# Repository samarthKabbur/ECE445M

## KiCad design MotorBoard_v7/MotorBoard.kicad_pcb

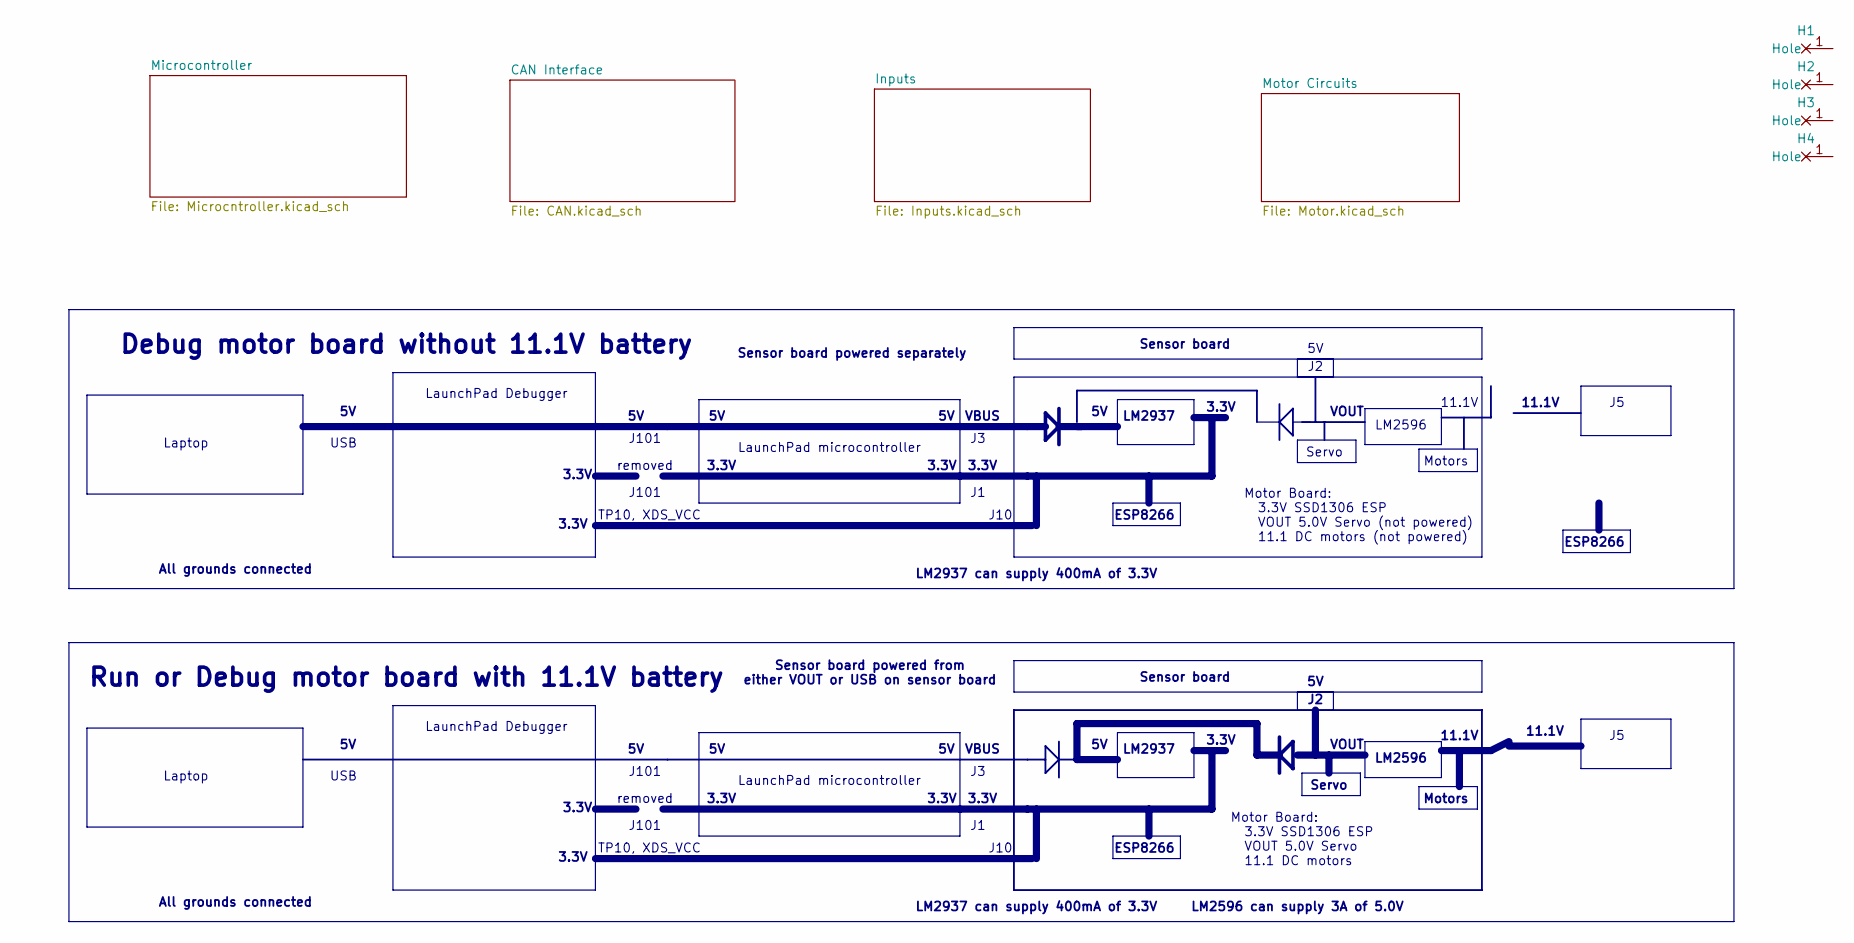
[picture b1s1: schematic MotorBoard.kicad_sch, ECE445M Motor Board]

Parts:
H1, H2, H3, H4: MountingHole_4_40

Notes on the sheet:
3.3V
LM2937 can supply 400mA of 3.3V
Motors
LaunchPad Debugger
USB
Laptop
VOUT
Debug motor board without 11.1V battery
Sensor board
Motor Board: 3.3V SSD1306 ESP VOUT 5.0V Servo 11.1 DC motors
Servo
LM2596 can supply 3A of 5.0V
VBUS
All grounds connected
J10
LM2937
LaunchPad microcontroller
removed
11.1V
Sensor board powered separately
LM2596
TP10, XDS_VCC
Run or Debug motor board with 11.1V battery
J101
Sensor board powered from either VOUT or USB on sensor board
Motor Board: 3.3V SSD1306 ESP VOUT 5.0V Servo (not powered) 11.1 DC motors (not powered)
ESP8266

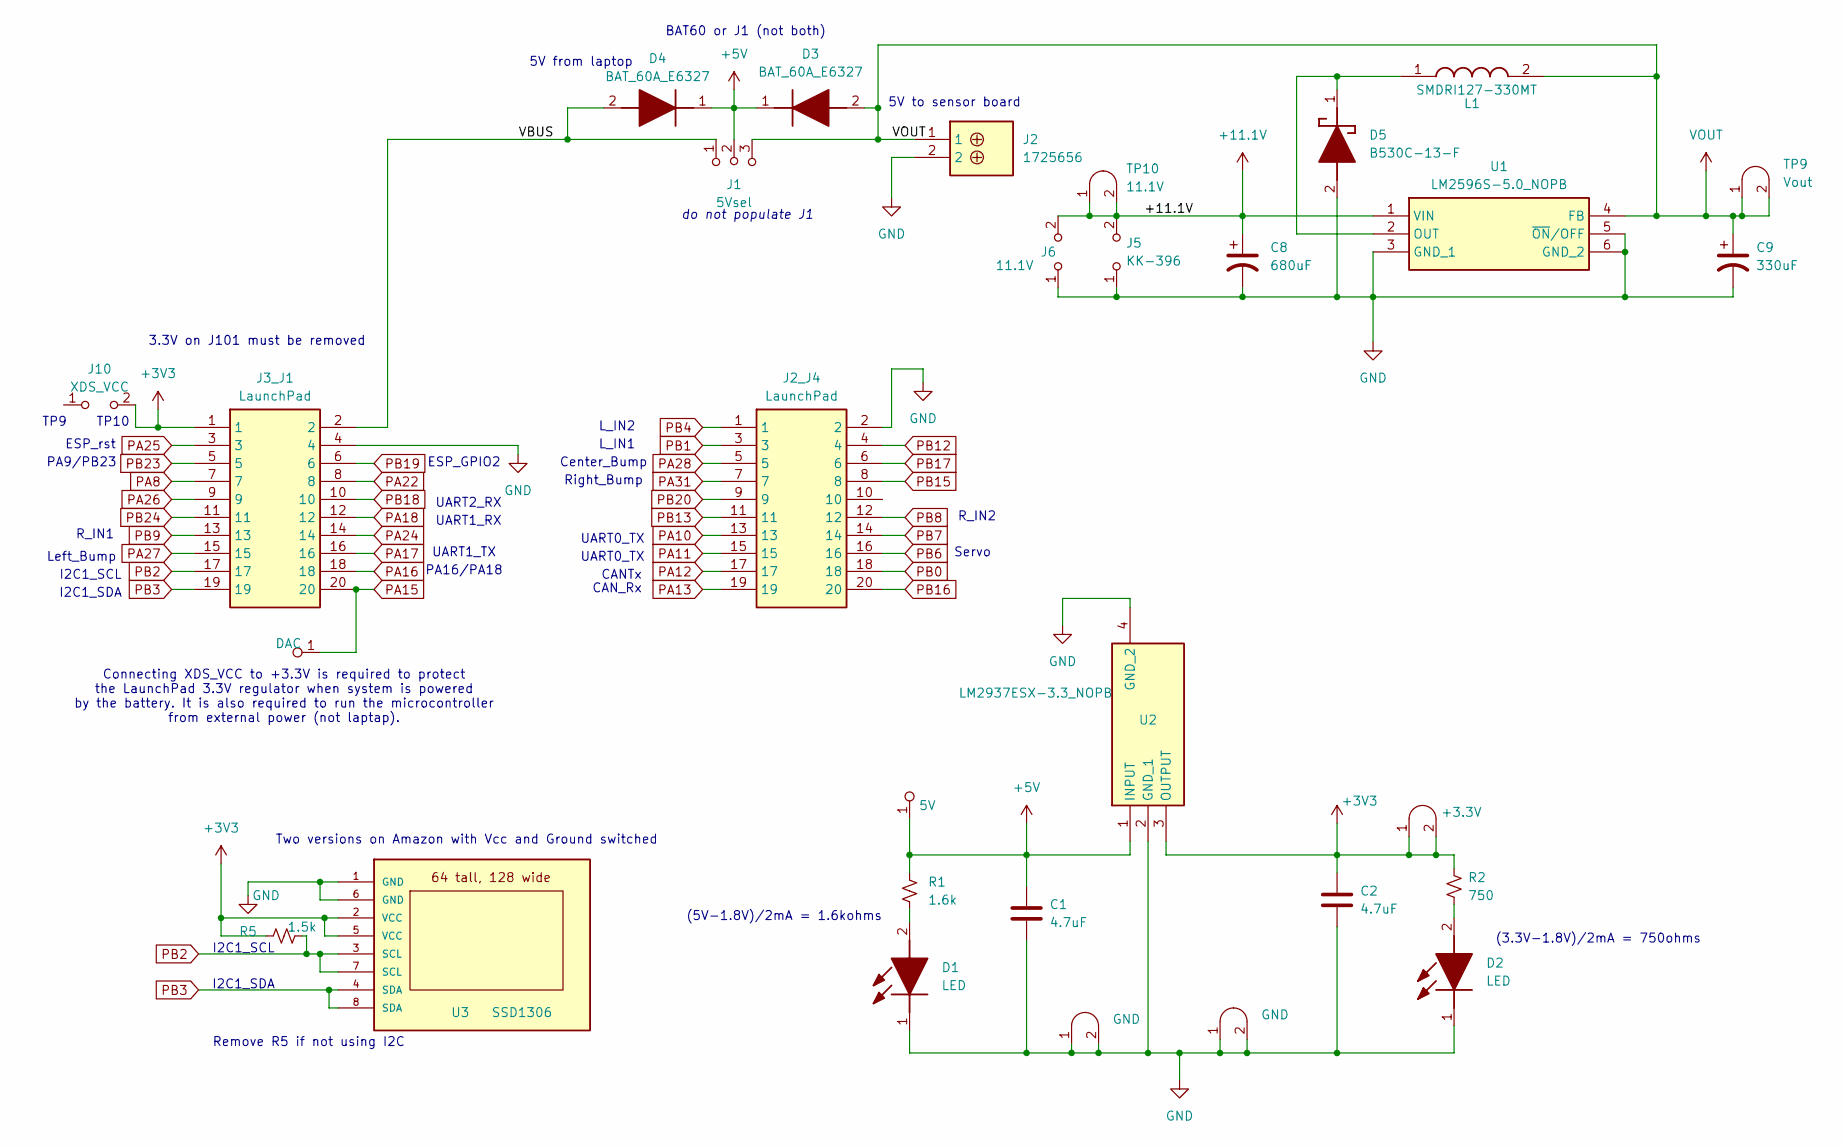
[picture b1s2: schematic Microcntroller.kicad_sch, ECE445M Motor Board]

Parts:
C1, C2: 4.7uF; C_0805_2012Metric; LCSC C5186689
C8: 680uF; CP_Elec_10x10.5; LCSC C2980172
C9: 330uF; CP_Elec_10x10.5; LCSC C5155335
D1, D2: LED; APT1608CGCK; Mouser Part Number 604-APTD1608LSECKJ3F
D3, D4: BAT_60A_E6327; SOD2513X110N; Mouser Part Number 726-BAT60AE6327
D5: B530C-13-F; DO-214AB; Mouser Part Number 621-B530C-13-F
J1: 5Vsel; PinHeader_1x03_P2.54mm_Vertical
J2: 1725656; Mouser Part Number 651-1725656
J2_J4, J3_J1: LaunchPad; Mouser Part Number 855-M20-8761042P
J5: KK-396; Molex_KK-396_A-41792-0002_1x02_P3.96mm_Horizontal
J6: 11.1V; PinHeader_1x02_P2.54mm_Vertical
J10: XDS_VCC; PinHeader_1x02_P2.54mm_Vertical
L1: SMDRI127-330MT; INDPM120120X800N; Mouser Part Number 851-CDRH127LDNP330MC
R1: 1.6k; R_0603_1608Metric; LCSC C340542
R2: 750; R_0603_1608Metric; LCSC C340542
R5: 1.5k; R_0603_1608Metric; LCSC C340542
TP1: DAC; Testpoint_1x1; Digikey 36-5000-ND, 36-5001-ND, 36-5002-ND , 36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
TP2: 5V; Testpoint_1x1; Digikey 36-5000-ND, 36-5001-ND, 36-5002-ND , 36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
TP3: +3.3V; Testpoint_1x02_P2.54mm; Digikey 36-5000-ND, 36-5001-ND, 36-5002-ND , 36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
TP9: Vout; Testpoint_1x02_P2.54mm
TP10: 11.1V; Testpoint_1x02_P2.54mm
TP11, TP16: GND; Testpoint_1x02_P2.54mm
U1: LM2596S-5.0_NOPB; KTT0005B; Mouser Part Number 926-LM2596S-5.0/NOPB
U2: LM2937ESX-3.3_NOPB; SOT230P700X180-4N; Mouser Part Number 926-LM2937IMP3.3NOPB
U3: SSD1306

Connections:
+3V3: C2.1, J3_J1.1, J10.2 (B), R2.1, R5.1, TP3.1 (A), TP3.2 (B), U2.3 (OUTPUT), U3.2 (VCC), U3.5 (VCC); also elsewhere on the board
+5V: C1.1, D3.1 (K), D4.1 (K), J1.2 (B), R1.1, TP2.1 (A), U2.1 (INPUT); also elsewhere on the board
+11.1V: C8.1, J5.2 (B), J6.2 (B), TP10.1 (A), TP10.2 (B), U1.1 (VIN); also elsewhere on the board
/Microcontroller/VBUS: D4.2 (A), J1.1 (A), J3_J1.2
GND: C1.2, C2.2, C8.2, C9.2, D1.1 (K), D2.1 (K), D5.2 (A), J2.2, J2_J4.2, J3_J1.4, J5.1 (A), J6.1 (A), TP11.1 (A), TP11.2 (B), TP16.1 (A), TP16.2 (B), U1.3 (GND_1), U1.5 (~ON/OFF), U1.6 (GND_2), U2.2 (GND_1), U2.4 (GND_2), U3.1 (GND), U3.6 (GND); also elsewhere on the board
unnamed: D1.2 (A), R1.2
unnamed: D2.2 (A), R2.2
unnamed: D5.1 (K), L1.1, U1.2 (OUT)
PA8: J3_J1.7
PA10: J2_J4.13
PA11: J2_J4.15
PA12: J2_J4.17; also elsewhere on the board
PA13: J2_J4.19; also elsewhere on the board
PA15: J3_J1.20, TP1.1 (A)
PA16: J3_J1.18
PA17: J3_J1.16; also elsewhere on the board
PA18: J3_J1.12; also elsewhere on the board
PA22: J3_J1.8
PA24: J3_J1.14
PA25: J3_J1.3; also elsewhere on the board
PA26: J3_J1.9
PA27: J3_J1.15; also elsewhere on the board
PA28: J2_J4.5; also elsewhere on the board
PA31: J2_J4.7; also elsewhere on the board
PB0: J2_J4.18
PB1: J2_J4.3; also elsewhere on the board
PB2: J3_J1.17, R5.2, U3.3 (SCL), U3.7 (SCL)
PB3: J3_J1.19, U3.4 (SDA), U3.8 (SDA)
PB4: J2_J4.1; also elsewhere on the board
PB6: J2_J4.16; also elsewhere on the board
PB7: J2_J4.14
PB8: J2_J4.12; also elsewhere on the board
PB9: J3_J1.13; also elsewhere on the board
PB12: J2_J4.4
PB13: J2_J4.11
PB15: J2_J4.8
PB16: J2_J4.20
PB17: J2_J4.6
PB18: J3_J1.10
PB19: J3_J1.6; also elsewhere on the board
PB20: J2_J4.9
PB23: J3_J1.5
PB24: J3_J1.11
VOUT: C9.1, D3.2 (A), J1.3 (C), J2.1, L1.2, TP9.1 (A), TP9.2 (B), U1.4 (FB); also elsewhere on the board

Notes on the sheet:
TP10
UART0_TX
UART1_RX
(5V-1.8V)/2mA = 1.6kohms
(3.3V-1.8V)/2mA = 750ohms
Left_Bump
5V from laptop
ESP_GPIO2
UART2_RX
CANTx
UART1_TX
Right_Bump
3.3V on J101 must be removed
L_IN1
Servo
Center_Bump
I2C1_SDA
PA16/PA18
BAT60 or J1 (not both)
Remove R5 if not using I2C
TP9
do not populate J1
R_IN2
PA9/PB23
I2C1_SCL
5V to sensor board
R_IN1
CAN_Rx
ESP_rst
Two versions on Amazon with Vcc and Ground switched
Connecting XDS_VCC to +3.3V is required to protect the LaunchPad 3.3V regulator when system is powered by the battery. It is also required to run the microcontroller from external power (not laptap).
L_IN2

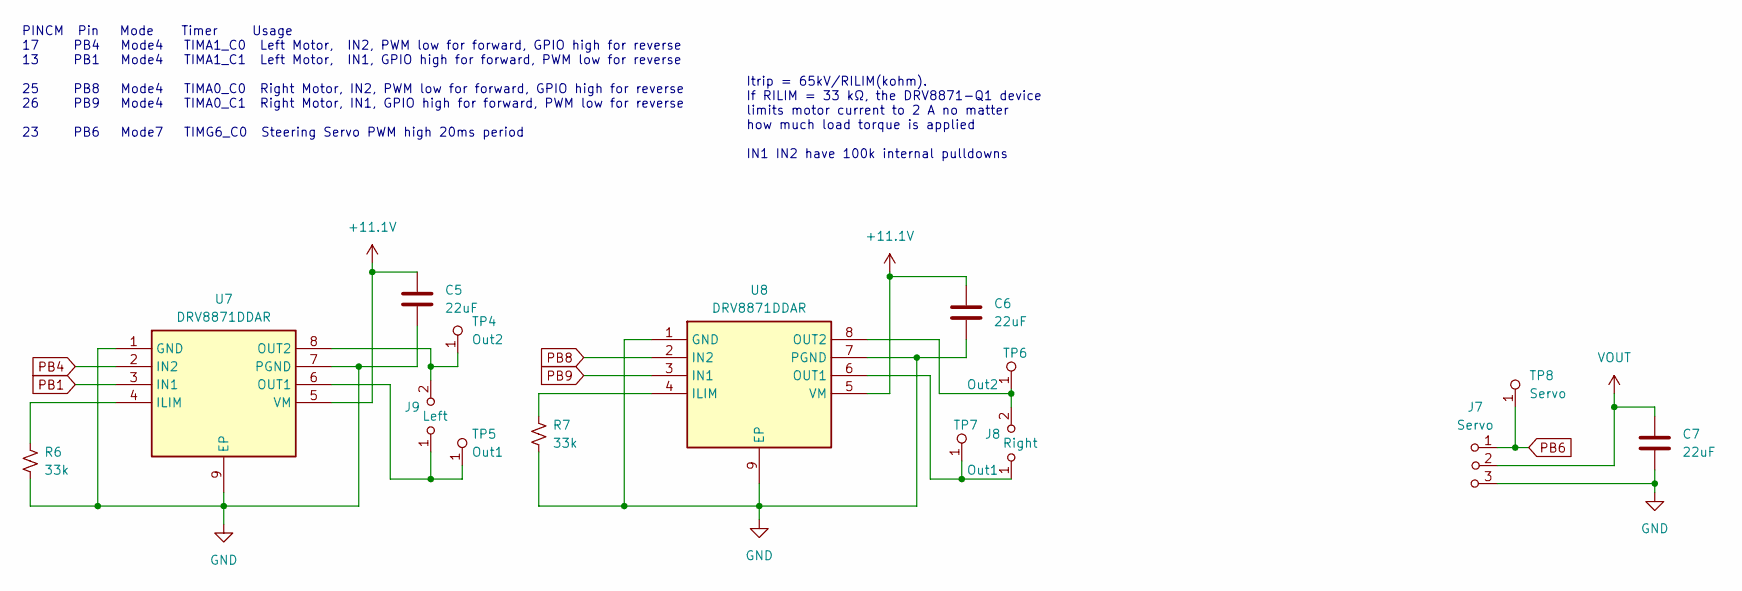
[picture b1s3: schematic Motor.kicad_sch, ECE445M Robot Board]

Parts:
C5, C6, C7: 22uF; C_0805_2012Metric; LCSC C5186689
J7: Servo; PinHeader_1x03_P2.54mm_Vertical
J8: Right; Molex_KK-396_5273-02A_1x02_P3.96mm_Vertical
J9: Left; Molex_KK-396_5273-02A_1x02_P3.96mm_Vertical
R6, R7: 33k; R_0603_1608Metric; LCSC C340542
TP4, TP6: Out2; Testpoint_1x1; Digikey 36-5000-ND, 36-5001-ND, 36-5002-ND , 36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
TP5, TP7: Out1; Testpoint_1x1; Digikey 36-5000-ND, 36-5001-ND, 36-5002-ND , 36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
TP8: Servo; Testpoint_1x1; Digikey 36-5000-ND, 36-5001-ND, 36-5002-ND , 36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
U7, U8: DRV8871DDAR; SOIC127P600X170-9N; Mouser Part Number 595-DRV8871DDAR

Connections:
+11.1V: C5.1, C6.1, U7.5 (VM), U8.5 (VM); also elsewhere on the board
GND: C5.2, C6.2, C7.2, J7.3 (C), R6.2, R7.2, U7.1 (GND), U7.7 (PGND), U7.9 (EP), U8.1 (GND), U8.7 (PGND), U8.9 (EP); also elsewhere on the board
unnamed: J8.1 (A), TP7.1 (A), U8.6 (OUT1)
unnamed: J8.2 (B), TP6.1 (A), U8.8 (OUT2)
unnamed: J9.1 (A), TP5.1 (A), U7.6 (OUT1)
unnamed: J9.2 (B), TP4.1 (A), U7.8 (OUT2)
unnamed: R6.1, U7.4 (ILIM)
unnamed: R7.1, U8.4 (ILIM)
PB1: U7.3 (IN1); also elsewhere on the board
PB4: U7.2 (IN2); also elsewhere on the board
PB6: J7.1 (A), TP8.1 (A); also elsewhere on the board
PB8: U8.2 (IN2); also elsewhere on the board
PB9: U8.3 (IN1); also elsewhere on the board
VOUT: C7.1, J7.2 (B); also elsewhere on the board

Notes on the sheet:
PINCM Pin Mode Timer Usage 17 PB4 Mode4 TIMA1_C0 Left Motor, IN2, PWM low for forward, GPIO high for reverse 13 PB1 Mode4 TIMA1_C1 Left Motor, IN1, GPIO high for forward, PWM low for reverse 25 PB8 Mode4 TIMA0_C0 Right Motor, IN2, PWM low for forward, GPIO high for reverse 26 PB9 Mode4 TIMA0_C1 Rig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
Itrip = 65kV/RILIM(kohm). If RILIM = 33 kΩ, the DRV8871-Q1 device limits motor current to 2 A no matter how much load torque is applied IN1 IN2 have 100k internal pulldowns

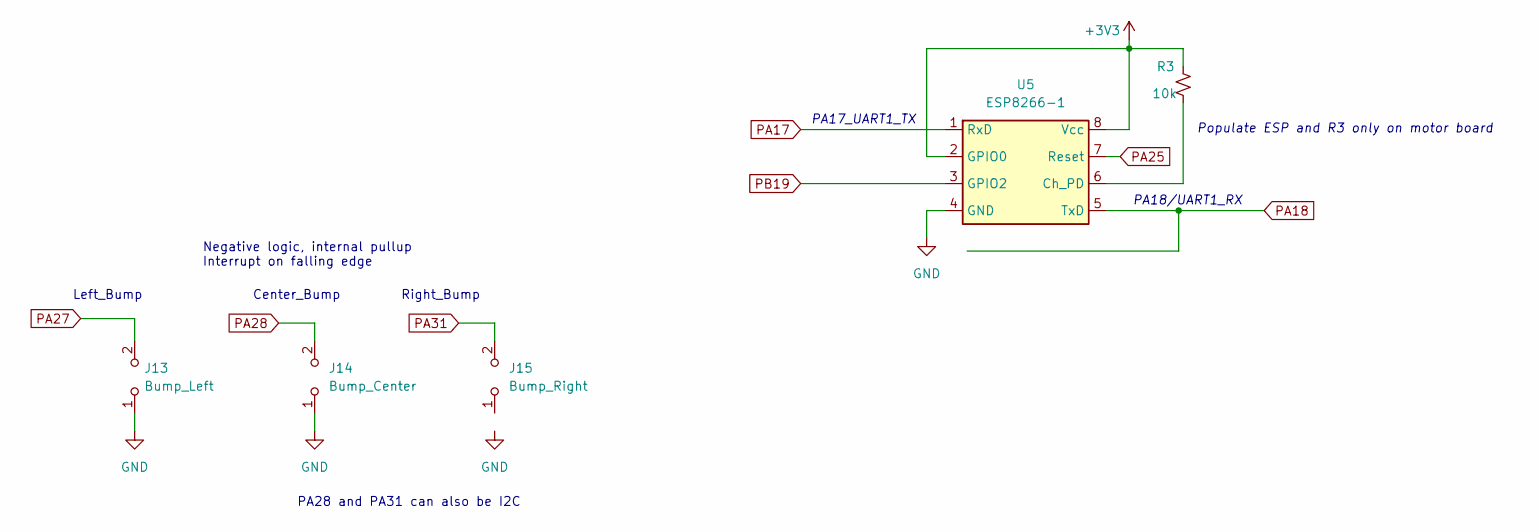
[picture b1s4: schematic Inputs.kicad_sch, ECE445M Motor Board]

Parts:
J13: Bump_Left; PinHeader_1x02_P2.54mm_Vertical
J14: Bump_Center; PinHeader_1x02_P2.54mm_Vertical
J15: Bump_Right; PinHeader_1x02_P2.54mm_Vertical
R3: 10k; R_0603_1608Metric
U5: ESP8266-1; PinHeader_2x04_P2.54mm_Vertical

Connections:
+3V3: R3.1, U5.2 (GPIO0), U5.8 (Vcc); also elsewhere on the board
GND: J13.1 (A), J14.1 (A), U5.4 (GND); also elsewhere on the board
unnamed: R3.2, U5.6 (Ch_PD)
PA17: U5.1 (RxD); also elsewhere on the board
PA18: U5.5 (TxD); also elsewhere on the board
PA25: U5.7 (Reset); also elsewhere on the board
PA27: J13.2 (B); also elsewhere on the board
PA28: J14.2 (B); also elsewhere on the board
PA31: J15.2 (B); also elsewhere on the board
PB19: U5.3 (GPIO2); also elsewhere on the board

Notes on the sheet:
Center_Bump
Populate ESP and R3 only on motor board
PA17_UART1_TX
PA18/UART1_RX
PA28 and PA31 can also be I2C
Negative logic, internal pullup Interrupt on falling edge
Left_Bump
Right_Bump

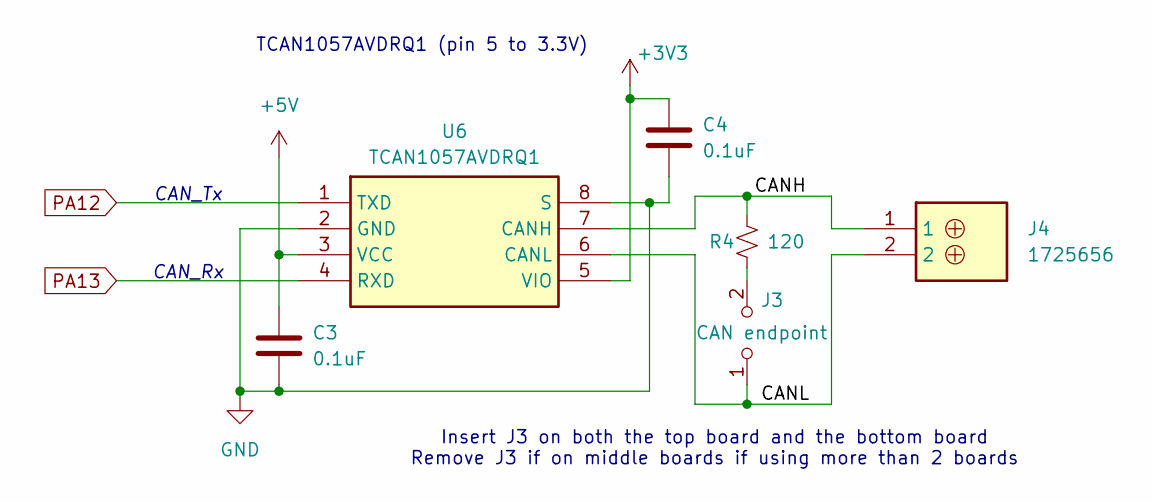
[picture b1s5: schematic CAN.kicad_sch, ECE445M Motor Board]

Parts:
C3, C4: 0.1uF; C_0603_1608Metric; LCSC C5186689
J3: CAN endpoint; PinHeader_1x02_P2.54mm_Vertical
J4: 1725656; Mouser Part Number 651-1725656
R4: 120; R_0603_1608Metric; LCSC C340542
U6: TCAN1057AVDRQ1; SOIC127P600X175-8N; Mouser Part Number 595-TCAN1057AVDRQ1

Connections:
+3V3: C4.1, U6.5 (VIO); also elsewhere on the board
+5V: C3.1, U6.3 (VCC); also elsewhere on the board
/CAN Interface/CANH: J4.1, R4.1, U6.7 (CANH)
/CAN Interface/CANL: J3.1 (A), J4.2, U6.6 (CANL)
GND: C3.2, C4.2, U6.2 (GND), U6.8 (S); also elsewhere on the board
unnamed: J3.2 (B), R4.2
PA12: U6.1 (TXD); also elsewhere on the board
PA13: U6.4 (RXD); also elsewhere on the board

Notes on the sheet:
Insert J3 on both the top board and the bottom board Remove J3 if on middle boards if using more than 2 boards
CAN_Tx
TCAN1057AVDRQ1 (pin 5 to 3.3V)
CAN_Rx

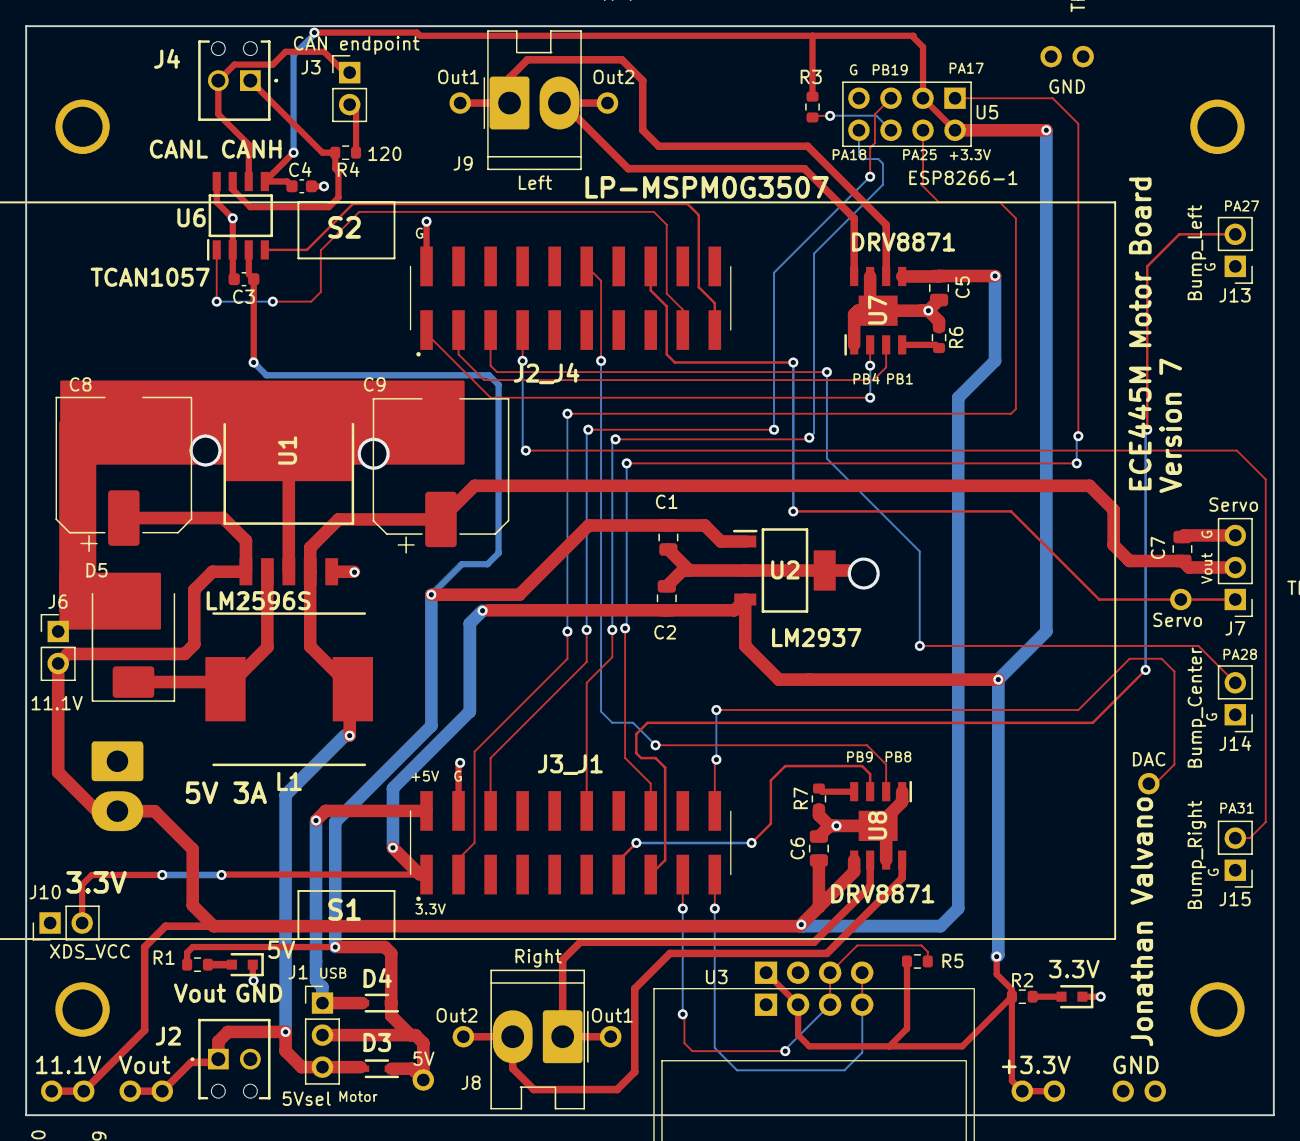
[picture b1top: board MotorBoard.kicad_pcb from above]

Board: 2 copper layers, 98.9 x 86.4 mm, 60 parts (1 on the bottom side), 36 nets.

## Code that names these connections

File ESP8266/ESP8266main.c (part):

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 |                        4   5 |
 \------------------------------/ 
 Connects MSPM0 
    UART1 on (PA17/PA18) or UART2 on (PB17/PB18)
    Reset on PA25
    Ok to not access PB19 because of the internal pullup in ESP8266
 ESP8266    MSPM0     Motor board version 7
  1 URxD    PA17      UART1 out of MSPM0, into ESP8266 115200 baud
  2 GPIO0             +3.3V for normal operation (ground to flash)
  3 GPIO2   PB19      GPIO, high/float on startup, has internal pullup, can be used for I/O
  4 GND     Gnd       GND (70mA)
  5 UTxD    PA18      UART out of ESP8266, UART1 into MSPM0 115200 baud
  6 Ch_PD             chip select, 10k resistor to 3.3V
  7 Reset   PA25      MSPM0 GPIO output, can issue output low to cause hardware reset
  8 Vcc               regulated 3.3V supply with at least 70mA

 ESP8266    MSPM0     Motor board version 7.1
  1 URxD    PB17      UART2 out of MSPM0, into ESP8266 115200 baud
  2 GPIO0             +3.3V for normal operation (ground to flash)
  3 GPIO2   PB19      GPIO, high/float on startup, has internal pullup, can be used for I/O
  4 GND     Gnd       GND (70mA)
  5 UTxD    PB18      UART out of ESP8266, UART2 into MSPM0 115200 baud
  6 Ch_PD             chip select, 10k resistor to 3.3V
  7 Reset   PA25      MSPM0 GPIO output, can issue output low to cause hardware reset
  8 Vcc               regulated 3.3V supply with at least 70mA
 */
 /* Derived from i2c_controller_rw_multibyte_fifo_poll_LP_MSPM0G3507_nortos_ticlang
  VCC to +3.3V
  I2C SCL: PB2 is the SSD1306 SCL, with 1.5k pullup to 3.3V
  I2C SDA: PB3 is the SSD1306 SDA
  GND to GND
*/

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
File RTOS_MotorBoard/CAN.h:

// CAN.h
// Runs on MSPM0G3507
// Use FDCAN0 to communicate on CAN bus PA12 and PA13
// 

// Jonathan Valvano
// December 11, 2025
// derived from can_to_uart_bridge_LP_MSPM0G3507_nortos_ticlang
/* 
 Copyright 2025 by Jonathan W. Valvano, valvano@mail.utexas.edu
    You may use, edit, run or distribute this file
    as long as the above copyright notice remains
 THIS SOFTWARE IS PROVIDED "AS IS".  NO WARRANTIES, WHETHER EXPRESS, IMPLIED
 OR STATUTORY, INCLUDING, BUT NOT LIMITED TO, IMPLIED WARRANTIES OF
 MERCHANTABILITY AND FITNESS FOR A PARTICULAR PURPOSE APPLY TO THIS SOFTWARE.
 VALVANO SHALL NOT, IN ANY CIRCUMSTANCES, BE LIABLE FOR SPECIAL, INCIDENTAL,
 OR CONSEQUENTIAL DAMAGES, FOR ANY REASON WHATSOEVER.
 For more information about my classes, my research, and my books, see
 http://users.ece.utexas.edu/~valvano/
 */
// Use TCAN1057AVDRQ1 (not TCAN1057A-Q1, the version with pin 5 nc)
//  Pin1 TXD  ---- CAN_Tx PA12 FD-CAN module 0 transmit
//  Pin2 Vss  ---- ground
//  Pin3 VCC  ---- +5V with 0.1uF cap to ground
//  Pin4 RXD  ---- CAN_Rx PA13 FD-CAN module 0 receive (0 to 3.3V)
//  Pin5 VIO  ---- +3.3V (digital interface supply)
//  Pin6 CANL ---- to other CANL on network 
//  Pin7 CANH ---- to other CANH on network 
//  Pin8 RS   ---- ground, Slope-Control Input (maximum slew rate)
// 120 ohm across CANH, CANL on both ends of network

#ifndef __CAN_H__
#define __CAN_H__
#include "../RTOS_Labs_common/OS.h"
#include <stdint.h>

void CAN_Init(uint32_t priority);

void CAN_EnableInterrupts(uint32_t priority);

/*
// 0 if failure
// 1 if ok
int CAN_Send(uint32_t id, uint32_t dlc, uint8_t *data);

// Returns 1 if receive data is available
//         0 if no receive data ready
int CAN_CheckMail(void);

// if receive data is ready, gets the data and returns true
// if no receive data is ready, returns false
int CAN_GetMailNonBlock(uint32_t *id, uint32_t *dlc, uint8_t *data);

// if receive data is ready, gets the data 
// if no receive data is ready, it waits until it is ready
void CAN_GetMail(uint32_t *id, uint32_t *dlc, uint8_t *data);
*/

/***************Added Functionality**************/
// CAN functions can be called from anywhere
// These function will NOT block and wait

// Gets value from receive FIFO
// Returns 1 if successful
// Returns 0 if failed
uint32_t CAN_Get(uint32_t *data);
uint32_t CAN_Get_ID(uint32_t *data, uint32_t *id);

// Puts a value into the send FIFO
// Returns 1 if successful
// Returns 0 if failed
uint32_t CAN_Put(uint32_t id, uint32_t data);

// Should be power of 2
#define CANFIFORECEIVESIZE 16

/* CAN FIFO */
typedef struct CAN_Fifo {
  uint32_t PutI;
  uint32_t GetI;
  uint32_t data[CANFIFORECEIVESIZE];
} CAN_Fifo_t;

CAN_Fifo_t CAN_SendFifo;
CAN_Fifo_t CAN_ReceiveFifo;

Sema4_t CAN_Available;

#endif //  __CAN_H__

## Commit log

2026-01-29 lab 1 in progress
2026-01-30 removed comments
2026-01-30 finished lab 1
2026-02-02 started lab 2
2026-02-02 round robin thread switch works
2026-02-02 systick simply requests pendsv and utilizes tail chaining
2026-02-02 lab 2 done
2026-02-04 stop tracking unnecessary files
2026-02-04 lab 2.2 pre prep, currently hardfaults
2026-02-07 os_kill currently leads to hardfault
2026-02-08 os kill works
2026-02-08 lab 2-2 pre prep done
2026-02-09 background task scheduler works!
2026-02-09 add s2 task works
2026-02-09 lab2 interpreter.c-not checked
2026-02-09 implemented mailbox init
2026-02-09 implemented mailbox send
2026-02-09 implemented mailbox recv
2026-02-09 implemented fifo init and updated mailbox init
2026-02-09 implemented fifo get
2026-02-09 merged interpreter in
2026-02-09 fifo works
2026-02-09 added semaphores to software fifos
2026-02-09 updated software fifo with semaphores and added mailbox test case
2026-02-09 mail box works
2026-02-09 interpreter works
2026-02-09 testing display
2026-02-09 everything works lab 2 except jitter
2026-02-11 hard faulting
2026-02-11 stack initializes to amount defined in os addthread parameter. prevents hardfault
2026-02-14 implemented add s1 task
2026-02-14 added compile time switch for debugging instruments
2026-02-16 fixed some jitter and just added debugging
2026-02-16 jitter reduces when timg8=500 period
2026-02-16 still debugging jitter
2026-02-21 Implemented priority scheduler and sorted TCB insertion
2026-02-22 testmain3 works
2026-02-22 working on test4 only periodic priority done
2026-02-23 updated wait, signal, kill, scheduler
2026-02-23 test main 5 works
2026-02-23 Update OS.c before merging
2026-02-25 moving back to align with olyvia's branch
2026-02-25 not working testfifo
2026-02-25 Testmain 4, 5, FIFO all work
2026-02-25 testmain7
2026-02-25 interpreter changes for lab 3
2026-03-02 started lab 4
2026-03-03 previous lab 3 final commit and lab 4 interpret stuff
2026-03-04 fat and directory defined
2026-03-04 eFile_Init() written
2026-03-04 started writing format
2026-03-04 Update filesystem and interpreter changes
2026-03-05 updated directory functions
2026-03-07 bitmap and filesystem_t added
2026-03-07 wrote efile_create. replaced directory_t with filesystem_t across the program
2026-03-07 wrote efile_wopen
2026-03-08 read functions
2026-03-08 testmain2 works
2026-03-08 testmain3
2026-03-09 lab4 done but need to fix jitter
2026-03-09 cleared commented sections
2026-03-10 final lab 4
2026-03-13 add deadline
2026-03-13 wrote heap definition as static array
2026-03-20 wrote heap init
2026-03-20 untested malloc
2026-03-20 working on malloc merge
2026-03-21 wrote malloc
2026-03-21 updated malloc
2026-03-21 updates to malloc and add process
2026-03-21 wrote calloc
2026-03-21 wrote realloc and free
2026-03-22 all heap functions work
2026-03-22 os process functions
2026-03-22 corrected entrypoint
2026-03-22 wrote svc handler
2026-03-22 updated svc handler
2026-03-23 began writing dynamic allocation of thread stacks
2026-03-23 updated add process thread to dynamically allocate stack
2026-03-23 moving back to static allocation
2026-03-23 updated entry point
2026-03-23 applied patch to efile to prevent unsigned overflow in header
2026-03-23 load program works
2026-03-23 lab 5 interpreter
2026-03-23 updated svc handler to use semaphores and r4 & r5
2026-03-25 fail gracefully. dyanamic allocation of threads and processes
2026-03-25 working on fix lab5
2026-03-25 made heap bigger
2026-03-25 added lab 6 update starter files
2026-03-25 updated motorboard project
2026-03-30 each tfluna sensor works independently
2026-03-30 Clean build artifacts and update .gitignore
2026-03-30 Keep modifiedwifi changes and remove old lab files
2026-03-30 added tfluna to sensorboard project
2026-03-30 saving tfluna progress
2026-03-30 Add Makefile and .mk to .gitignore
2026-03-30 untracked some files
2026-03-30 saving
2026-03-31 updated gitignore
2026-03-31 Added small individual fifos for each tfluna sensor
2026-04-01 CAN test
2026-04-01 attemping to send multiple sensor data via mailbox
2026-04-01 three tf luna sensors
2026-04-01 CAN Fix
2026-04-02 Added WiFi thread with status + timing and cleaned project files
2026-04-03 tfluna 1, 2, and IR1, 2 all work simultaneously
2026-04-06 gitignore added
2026-04-06 testing can function
2026-04-06 CAN tests
2026-04-06 working on angle to wall calculation
2026-04-07 cleaned motor.c
2026-04-08 testing fixed point angle calculation
2026-04-08 updated os kill for svc handler
2026-04-08 basic controller done
2026-04-08 Commented out efile code
2026-04-08 updated algorithm and debug
2026-04-09 can and motor test 7a
2026-04-10 initial code writing
2026-04-10 took code from motors branch
2026-04-10 cleaned up code
2026-04-10 reverted virus detector
2026-04-12 increased stack size and fixed button thread bug
2026-04-12 testing calculate slope
2026-04-13 added can and pwm libraries to motorboard project
2026-04-13 sensor test works on track
2026-04-13 Wifi
2026-04-13 cleaned up code and implemented push button start
2026-04-13 Motors
2026-04-14 updated control algorithm to map continuous direction and speed
2026-04-15 CAN frame change
2026-04-15 CAN command change
2026-04-15 CAN change
2026-04-15 added button
2026-04-19 updated control algorithm based upon accurate point vectors
2026-04-19 updated structs
2026-04-20 checkout 7b motors with wifi
2026-04-20 updated debug print
2026-04-20 protect against div by zero
2026-04-20 pid implemented, untested on track
2026-04-20 motor.c changes to run with steering/differentials/speed
2026-04-20 updated sensor algorithm
2026-04-21 updated wifi and removed handle crash
2026-04-21 did some tuning
2026-04-21 added button start
2026-04-21 tuning
2026-04-21 button press works
2026-04-22 bumb switches work/go backwards when hit
2026-04-22 new turning logic
2026-04-22 happy with sensors pre race
2026-04-27 3rd place code
